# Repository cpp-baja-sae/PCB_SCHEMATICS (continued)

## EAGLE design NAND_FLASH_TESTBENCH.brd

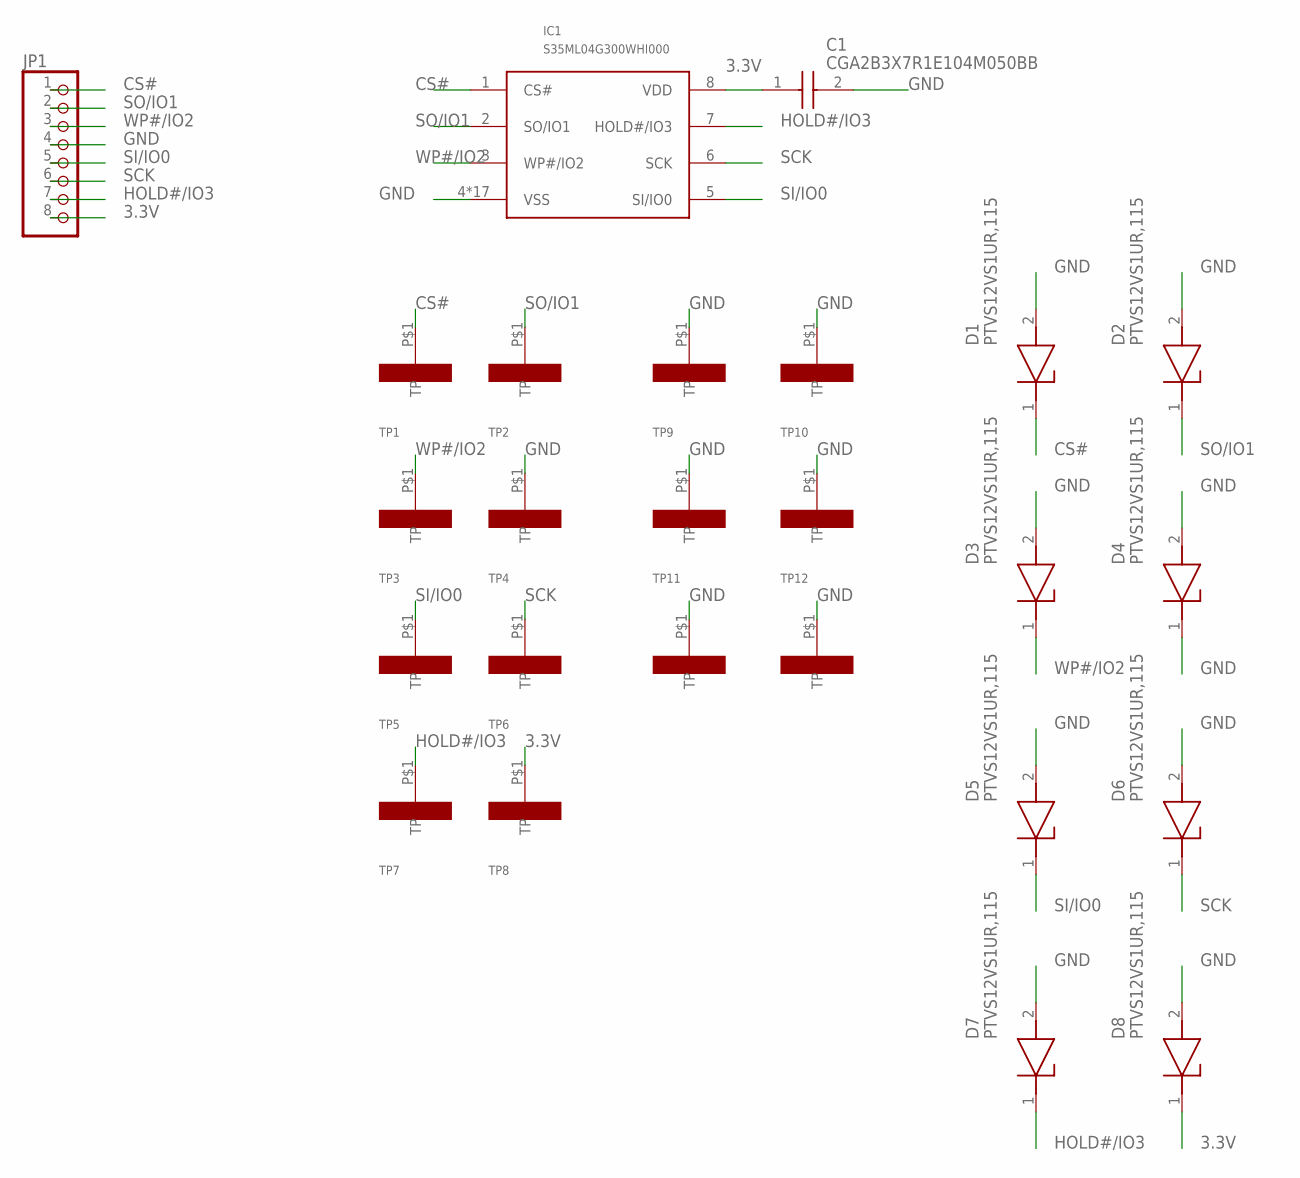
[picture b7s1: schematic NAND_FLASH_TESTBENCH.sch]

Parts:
C1: CGA2B3X7R1E104M050BB; CAPC1005X55N
D1, D2, D3, D4, D5, D6, D7, D8: PTVS12VS1UR,115; SOD123W
IC1: S35ML04G300WHI000
JP1: PINHD-1X8; 1X08
TP1, TP2, TP3, TP4, TP5, TP6, TP7, TP8, TP9, TP10, TP11, TP12, TP13, TP14: S1751-46R; 1.85X3.45_MM

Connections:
3.3V: C1.1, D8.1 (K), IC1.8 (VDD), JP1.8, TP8.P$1
CS#: D1.1 (K), IC1.1 (CS#), JP1.1, TP1.P$1
GND: C1.2, D1.2 (A), D2.2 (A), D3.2 (A), D4.1 (K), D4.2 (A), D5.2 (A), D6.2 (A), D7.2 (A), D8.2 (A), IC1.4 (VSS), IC1.P$1 (VSS), IC1.P$2 (VSS), IC1.P$3 (VSS), IC1.P$4 (VSS), IC1.P$5 (VSS), IC1.P$6 (VSS), IC1.P$7 (VSS), IC1.P$8 (VSS), IC1.P$9 (VSS), IC1.P$10 (VSS), IC1.P$11 (VSS), IC1.P$12 (VSS), IC1.P$13 (VSS), IC1.P$14 (VSS), IC1.P$15 (VSS), IC1.P$16 (VSS), JP1.4, TP4.P$1, TP9.P$1, TP10.P$1, TP11.P$1, TP12.P$1, TP13.P$1, TP14.P$1
HOLD#/IO3: D7.1 (K), IC1.7 (HOLD#/IO3), JP1.7, TP7.P$1
SCK: D6.1 (K), IC1.6 (SCK), JP1.6, TP6.P$1
SI/IO0: D5.1 (K), IC1.5 (SI/IO0), JP1.5, TP5.P$1
SO/IO1: D2.1 (K), IC1.2 (SO/IO1), JP1.2, TP2.P$1
WP#/IO2: D3.1 (K), IC1.3 (WP#/IO2), JP1.3, TP3.P$1

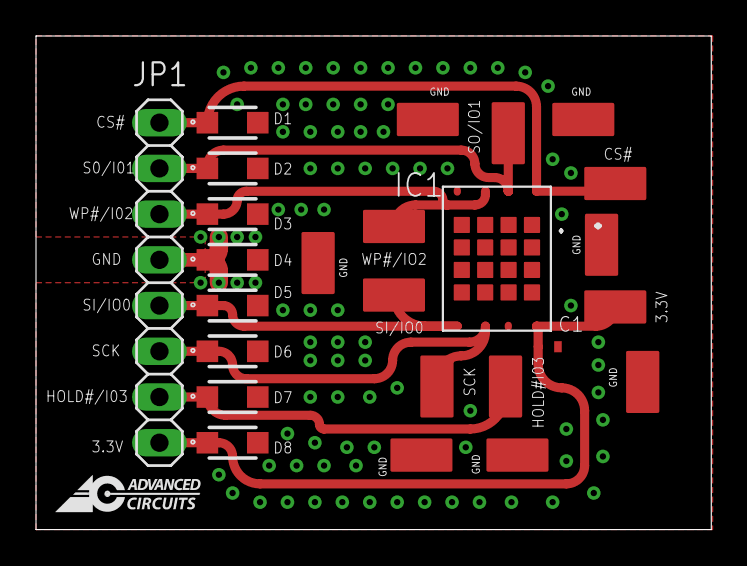
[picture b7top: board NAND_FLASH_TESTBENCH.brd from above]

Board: 2 copper layers, 37.5 x 27.4 mm, 25 parts (0 on the bottom side), 8 nets.

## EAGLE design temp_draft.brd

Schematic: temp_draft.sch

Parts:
C1: C0805C563K5RACAUTO; CAPC0805C563K
C2: C1206C155K5RACAUTO; CAPC1206C
C3: C1206C564J1RACAUTO; CAPC1206
C4: C1812C944KARLCAUTO; CAPC4532X380N
C5: C2220C664K1GLCAUTO; CAPC2220
C6: C0805C472F2GECAUTO; CAPC2012X100N
C7: GRM31C5C1H913JA01L; CAPC3216X180N
C8, C9, C10, C11: CGA3E2X7R1H104K080AE; CAPC1608X90N
IC1, IC2, IC3, IC4: NCS21911SN2T1G; SOT95P275X110-5N
JP2: PINHD-1X7; 1X07
LED1: 150080GS75000; LEDM2012X80N
R1: ERA-6AEB8451V; ERA6A_(0805)
R2, R9: ERA-8AEB3322V; ERA8A_(0805)
R3: ERA-6AED1243V; ERA6A_(0805)
R4: ERA-6AEB9091V; ERA6A_(0805)
R5: ERA-8AEB8250V; ERA8A_(0805)
R6: ERJ-P06J431V; ERJP06_(0805)
R7: TNPW080510K0BEEN; RESC2013X65N
R8, R10: RN73H2ATTD1043B25; ERA6A_(0805)
R11: PTS120601B1K00P100; PTS1206
R12: ERA-6ARW563V; ERA6A_(0805)
TP1, TP2, TP3, TP4, TP5, TP6, TP7, TP8, TP9, TP10: S1751-46R; 1.85X3.45_MM

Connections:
A1: C5.2, IC2.1 (OUT), IC2.4 (IN-), R8.1
A2: C3.2, IC3.1 (OUT), IC3.4 (IN-), R1.1
A3: C4.2, IC4.1 (OUT), IC4.4 (IN-), R7.1
BUFF: IC1.4 (IN-), R4.1, R5.1
GND: C1.2, C2.2, C6.2, C7.2, C8.2, C9.2, C10.2, C11.2, IC1.2 (VSS), IC2.2 (VSS), IC3.2 (VSS), IC4.2 (VSS), JP2.7, R5.2, R6.2, R11.2, TP5.P$1, TP6.P$1, TP7.P$1, TP8.P$1, TP10.P$1
INPUT1: IC1.3 (IN+), JP2.2, R11.1, R12.2, TP1.P$1
unnamed: IC1.1 (OUT), R2.1, R4.2
unnamed: C3.1, R8.2, R10.1
unnamed: C5.1, R2.2, R9.1
unnamed: C4.1, R1.2, R3.1
unnamed: LED1.1 (K), R6.1
OUTPUT1: C1.1, IC2.3 (IN+), JP2.3, R9.2, TP2.P$1
OUTPUT2: C6.1, IC3.3 (IN+), JP2.4, R10.2, TP3.P$1
OUTPUT3: C7.1, IC4.3 (IN+), JP2.5, R3.2, TP4.P$1
OUTPUT4: C2.1, JP2.6, R7.2, TP9.P$1
V_12V: C8.1, C9.1, C10.1, C11.1, IC1.5 (VDD), IC2.5 (VDD), IC3.5 (VDD), IC4.5 (VDD), JP2.1, LED1.2 (A), R12.1

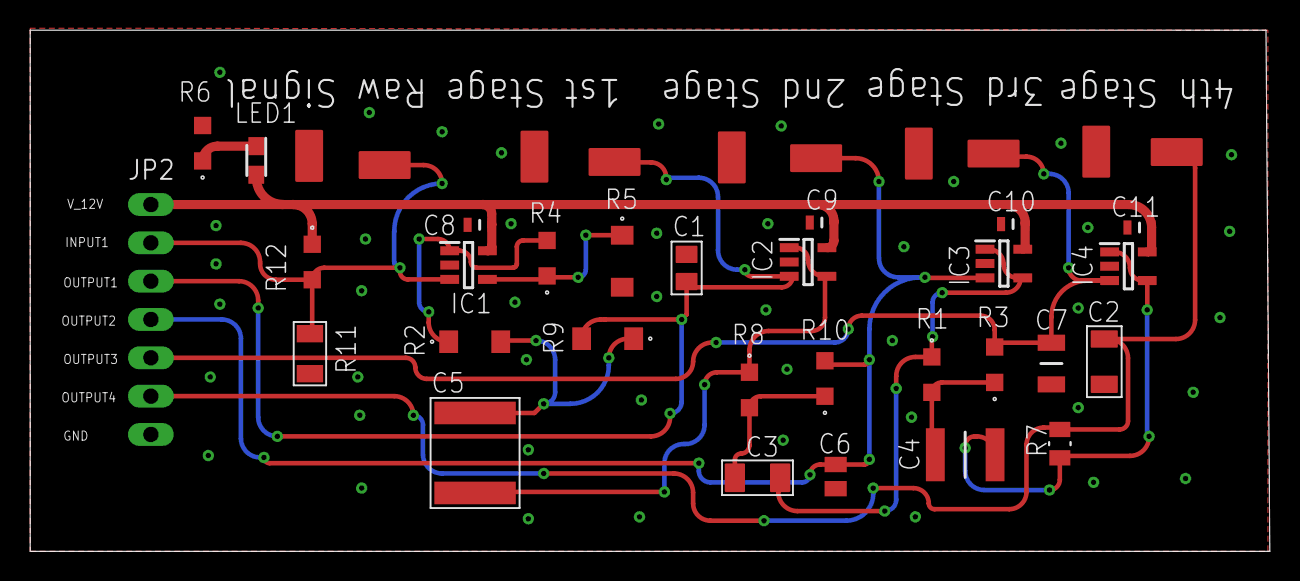
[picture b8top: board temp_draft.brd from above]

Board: 2 copper layers, 82.2 x 34.5 mm, 39 parts (1 on the bottom side), 16 nets.

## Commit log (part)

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2021-10-02 Rev 1
2021-10-02 Test change to verify functionality
2021-10-02 Empty README file
2021-10-02 Added README
2021-10-02 Created README
2021-10-02 Added ADC test bench
2021-10-02 Moved pcb to github
2021-10-02 Adding random Connector for testing
2021-10-07 Read me file is here
2021-10-07 pk fire
2021-10-07 branch created!
2021-10-07 added files!
2021-10-07 Creating a schematic file for LTC4222
2021-10-08 readme file
2021-10-08 This is my first commit
2021-10-08 Help
2021-10-09 This is my second PCB for opamp test bench
2021-10-09 Added comments on schematics
2021-10-10 This is my third PCB for opamp test bench
2021-10-13 New branch created based off rev 1
2021-10-13 PCB test bench fourth version
2021-10-13 Repo clean up
2021-10-15 PCB test bench fifth version
2021-10-15 sch rev_1
2021-10-15 began base layout of new STM32 controller
2021-10-15 saved
2021-10-15 rev_2 ready for layout, sch part incomplete info
2021-10-15 Not much changed
2021-10-15 pcb test bench 6th version
2021-10-15 settings update
2021-10-15 base board layout, done
2021-10-15 pcb test bench 7th version
2021-10-16 added GND components for board
2021-10-17 with LED and tented Vias
2021-10-17 PCB test bench version 8th
2021-10-18 changed vias to GND vias
2021-10-19 Created Gerber file
2021-10-20 Created files for Sending to manufacturing
2021-10-22 Created Gerber
2021-10-22 Added LTC4222
2021-10-22 Add LTC4222
2021-10-23 LTC4222 Version 1.0 w/o flip flop
2021-10-25 Strain gauge adc page nearly updated
2021-10-27 Adjusted the LTC4222 to incorporate new 10k Ohm resistor after the first went out of stock
2021-10-27 no changes
2021-10-29 Added the D Flip-Flop and XOR Gate to the Schematic
2021-10-29 Forgot to save the first time
2021-11-01 LTC4222 Schematic Design V2
2021-11-02 Polished LTC4222 schematic and added test points. Started on pin heads
2021-11-02 Schematics done and capacitors have 3d packages
2021-11-02 random updated eagle.epf
2021-11-03 Created readme branch
2021-11-03 Created eagle file
2021-11-03 Created single LTC4222 setup
2021-11-03 2 Efuses are on board now with seperate net names
2021-11-03 Added ADM1177 and power reg with some pin headers
2021-11-04 Schematic is laid out, missing test points and connector, nearly ready for board layout
2021-11-04 added a eagle.epf file???
2021-11-04 added some test points
2021-11-06 LTC4222 V3; Finished up the headers; Need to source LEDs and LED resistors; Final step = MUX: Check up with Forrest about LDO after final step
2021-11-06 Finished The 8G_Accelerometer, awaiting review from FOrrest FOr final revision
2021-11-09 Schematics have been finsihed, now moving into layout
2021-11-09 Began some base layout, found R2k came from wrong library, need to fix
2021-11-09 ~60% through layout
2021-11-17 Save before moving from 2-layer to 4-layer instead
2021-11-24 Final board done, maybe for feedback from Forrest
2021-11-24 Began 4 layer layout
2021-12-21 No real changes made yet, moving between projects
2021-12-21 This is the inception of revision 2 based off of revision 1.
2022-01-13 Close to finsihing
2022-01-14 Needs final labeling touch ups
2022-01-27 Near finalized board
2022-01-27 Added power leds and labels, -Ready for manufacturing
2022-01-28 Beginning Analog 40G Revision 2
2022-01-29 First draft of 40G Accel Rev 2. Need to change hole size
2022-01-30 Final Design waiting for Forrest's Analysis - Subject to changes
2022-01-31 Initial PCB design
2022-02-01 Added ground plane to board
2022-02-01 Trying to add a ground plane that actually connects to all of the ground points
2022-02-01 Changed board layout
2022-02-04 README
2022-02-05 eagle file added
2022-02-05 no changes made
2022-02-05 New revision of board layout and fixed power connections to buffers in schematic.
2022-02-06 created NANO_FLASH part
2022-02-06 Fix connection of part placement
2022-02-06 Began working on the PCB schematic and actually saving on git
2022-02-06 Reconnected pins for part
2022-02-06 fixed connections of 16 pads
2022-02-06 fixed labels
2022-02-06 Just 2 airwires left to connect, waiting for Forrest Review
2022-02-06 finished board layout
2022-02-06 minor changes to text
2022-02-06 New layout for PCB board. Added diodes to main board pins. Ground stitching vias added. Ready for final review.
2022-02-06 Changes to component label placement. Addition of more ground vias where room was found. Change in routing for power to X buffer
2022-02-06 Board Layout
2022-02-06 sch of board
2022-02-06 No Errors on the board waiting for Forrest to confirm and explain what pin 9 EP is
2022-02-07 NO errors Everything done and connected, PCB Design has been completed now waiting for Forrest's Review, if HE approves then done if not this is just a draft
2022-02-07 updated layout
2022-02-07 board
2022-02-07 Widened GND path near diode. Enlarged Z dot for board orientation.
2022-02-07 Adjusted positions of axis labels.
2022-02-07 Changed LDO input cap and LDO to parts that are in stock.
2022-02-07 board rev_1
2022-02-07 FInal PCB, some parts might be bought using diff website if not PCB will be revised for later deadline
2022-02-07 added dot
2022-02-07 FINAL BOARD DONEgit add --all!
2022-02-09 FInal PCB going for manufacturing
2022-02-10 Test message V2
2022-02-10 Testing git push again
2022-02-11 Small alterations
2022-02-12 PCB Design V1
2022-02-12 Added informational text to schematic. No changes to board.
2022-02-12 PCB schematic V1.2
2022-02-15 LTC4222 v1.9; requires ground vias everywhere; idk how to un ratsnets the ground
2022-02-15 LTC4222 V2
2022-02-16 Updated components to have 3D models.
2022-02-19 Added Advance circuits logo and gerber file
2022-02-20 updated labels
2022-03-02 Added 3D model for microcontroller
2022-03-03 Minor additions
2022-03-03 progress
2022-03-04 bom lists
2022-03-05 Minor updates
2022-03-06 Moving to Desktop
2022-03-08 just changing boards
2022-03-09 added power rails
2022-03-11 moving computers
2022-03-15 General E-fuse done
2022-03-15 mass added e-fuse
2022-03-16 Moving directories
2022-03-16 E-fuse is about done, started on temp sensors
2022-03-20 This is the readme
2022-03-20 board is ready for schematic review
2022-03-20 Working on QSPI
2022-03-20 Added new readme to pwr supply branch
2022-03-20 Created new branch and added readme
2022-03-20 Added all EAGLE files for PWR supply rev 1
2022-03-21 Added new componants to schematic and board layout
2022-03-21 Modified Board File
2022-03-24 movng pc
2022-03-24 update layout
2022-03-24 Preliminary Digital 40G Board Layout
2022-03-24 Modified Board Layout
2022-03-24 temp
2022-03-24 ready for routing
2022-03-24 Last wiring left to do then ready for board layout
2022-03-25 final routing for the night
2022-03-25 Modified Board
2022-03-25 Completed First Draft of Digital 40G Board Layout
2022-03-26 Checking main wire up
2022-03-26 Began board layout!
2022-03-26 Schematic done, ready for review, only needs com LED and test point, waiting till after routing to see if there is enough space to add extra hardware
2022-03-27 Smashing font
2022-03-27 Created BareBoardLayout for preliminary enclosure design
2022-03-27 safety save
2022-03-28 Made board layout more compact. used more backside of board
2022-03-28 gawd I hope I'm right...
2022-03-29 gawd I hope I'm right pt 2...
2022-03-29 Added Reverse Voltage Protection PMOS
2022-03-31 modiefied baord layout
2022-04-01 Final routing
2022-04-01 Board Complete
2022-04-01 Board Complete w/transformer cut out
2022-04-01 Actually finished i swear
2022-04-02 finished board routing
2022-04-02 Second Draft of Digital 40G Layout. Ready for review.
2022-04-02 modified routing
2022-04-02 Verifying the correct version of the board has been pushed for final review. There shoud be no changes since previous push.
2022-04-02 Final
2022-04-02 Vias are now tented
2022-04-02 modified traces to be curved.
2022-04-03 Modified Text Sizes of Test Points, Addeed more GND Vias, Added Mounting Holes
2022-04-03 Moved VIAS around and moved connector closer to center of boar
2022-04-04 Made board smaller
2022-04-04 modified PWR and GND planes for board layout
2022-04-04 reshaped board
2022-04-04 Final w/GND vias & Enclosure Holes
2022-04-04 changed GND planes. Ready for review
2022-04-04 Rearranged transformer
2022-04-04 this B better work
2022-04-04 Changed Trace Widths of Signals
2022-04-04 checked DRC and ERC. Ready for Review
2022-04-04 Feeling good, she better work
2022-04-04 Saving before battery dies
2022-04-05 Placed hardware for solidworks modeling
2022-04-05 Created solid works stripped model of board and setup main board to support layout
2022-04-05 Moving pc, finsihed layout of 7 e-fuses
2022-04-06 modified GND planes
2022-04-06 saw random error about invalid attribute ??? continuing on ward
2022-04-06 Check point
2022-04-06 Checkout point, efuses placed
2022-04-06 Saving
2022-04-06 Moving pc
2022-04-07 Doing dangerous moves
2022-04-07 Dangerous maneuvers currently... Board reshaping
2022-04-07 New shrunken board
2022-04-07 Connectors are moved to new locations, need to move mounting points
2022-04-07 Uploaded all necessary 3D models
2022-04-08 New board dimensions
2022-04-08 New solid works model
2022-04-08 swapping
2022-04-09 Fixed Flip-Flop Footprint/Pushed 3D Model
2022-04-09 Added more GND Vias, Changes text size, moved texts, clears DRC error
2022-04-09 Doing power supply review now
2022-04-09 Reverting to 8bc5c6813a7756360a086b87a4ec86a3b844c152 due to ULP script failure
2022-04-09 Near done with layout
2022-04-10 layout has been placed
2022-04-10 Reduced model
2022-04-11 Final Board Layout Update. Incorporated new connector model.
2022-04-12 Minor changes, should only been a change of board stack up
2022-04-13 Used SRC to change the LBR reference of each componant
2022-04-15 General new connectors save point
2022-04-16 switching
2022-04-16 Added CMRR Caps at CJ input (Finalized)
2022-04-16 Schematics added Flash memory and new 80 pin connectors, Moving to layout
2022-04-16 Modifed board. Connected GND planes Together.
2022-04-16 modified GND panes Isolation neat VIN connector
2022-04-16 Single efuse routed
2022-04-16 Save point
2022-04-17 new connector layout
2022-04-17 Save point, need to add buffer filter components
2022-04-18 Resized text, schematics have new filter layout
2022-04-18 Nearly ready to route
2022-04-18 Compoenets are fully laid out, beginning routing now
2022-04-18 Board reshaped, ready to route!
2022-04-18 via in pad set
2022-04-19 First layout steps
2022-04-19 Trying new routing
2022-04-19 new layout for routing
2022-04-19 4 efuses routed
2022-04-19 Left side routed
2022-04-20 Final board/3d model with delay trigger fix
2022-04-20 Final final board layout update. Screw mounted now.
2022-04-20 Final ERC fixes
2022-04-21 Routed analog filters
2022-04-21 save point, adding gnd nodes
2022-04-22 Eagle file
2022-04-22 Final final preliminary board layout update. Back to 2 screw holes and sized at 1.25 inches square.
2022-04-22 Added a couple of ground stitching vias
2022-04-22 Moving
2022-04-22 Switched to 2 layer board
2022-04-22 Night check point
2022-04-22 New layout. 2 layer board again. Updated 4PCB and regular version.
2022-04-23 ROUTING DONE
2022-04-23 Checked warnings on schematic, connected 40G input pin
2022-04-23 Wired last airwire, need to add test points for all signals and move silk screen labels
2022-04-23 Added bypass caps on logic gates and did one last review
2022-04-23 Adding test points
2022-04-23 Aligned test pads
2022-04-24 no air wires, need to relabel labels and position it
2022-04-24 Labels
2022-04-24 Labels arranged
2022-04-24 PC: modified Name placement
2022-04-24 nothing
2022-04-24 PC: Added vias under lt3579 for better thermals
2022-04-24 added new LED voltage clamps
2022-04-24 Need to add remaining logos and text
2022-04-24 Diff_AMP sch
2022-04-24 added Vref
2022-04-25 updated board
2022-04-25 Sending to Fab
2022-04-25 grabbing other files
2022-04-26 Generated Gerber file
2022-04-26 Generate Gerber file
2022-04-26 LAPTOP: Checked for changes, Pushed to Fusion 360
2022-04-26 Changed routing spacing to 5 mil
2022-04-26 Saftey save
2022-04-26 new routing
2022-04-27 new version sent for fab
2022-04-30 Ready for Rev
2022-05-01 rev_1
2022-05-01 revised
2022-05-01 Revision
2022-05-01 revisions
2022-05-02 Sent to Fab
2022-05-17 LAPTOP: changes unknown, pushing anyway
